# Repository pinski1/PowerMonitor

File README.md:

# Power Monitor
I wanted to monitor the current and voltage of some battery packs as I discharged them. As the battery packs were >36V fully charged there was no available board to do this easily. So here's one that's good for up to 80V.

This project is an entry into the [Hackaday.io](Hackaday.io) [Square Inch Project](https://hackaday.io/contest/160135-the-return-of-the-square-inch-project) Contest.

## Detailed Description

This project makes use of the Analog Devices [LTC4151](http://www.analog.com/en/products/monitor-control-protection/power-monitors/ltc4151.html) to measure the voltage, current and communicate these values over an I<sup>2</sup>C bus. In addition the LTC4151 will also calculate the instantaneous power and read an auxilary ADC input, in my board I've set this to be a temperature sensor.

### I<sup>2</sup>C Address
By default the I<sup>2</sup>C address is set to 0xD4 but if you wish to change it please consult this table:

|JP1|JP2|Address|
|----|----|----|
|X|X|0xCC|
|L|H|0xCE|
|H|NC|0xD0|
|H|H|0xD2|
|NC|NC|0xD4|
|L|NC|0xD6|
|H|L|0xD8|
|NC|H|0xDA|
|NC|L|0xDC|
|L|L|0xDE|

### Registers

|Register Address|Register Name|Read/Write|Description|
|--|--|--|--|
|0x00|SENSE (A)|R/W|ADC Current Sense Voltage Data (8 MSBs)|
|0x01|SENSE (B)|R/W|ADC Current Sense Voltage Data (4 LSBs)|
|0x02|VIN (C)|R/W|ADC VIN Voltage Data (8 MSBs)|
|0x03|VIN (D)|R/W|ADC VIN Voltage Data (4 LSBs)|
|0x04|ADIN (E)|R/W|ADC ADIN Voltage Data (8 MSBs)|
|0x05|ADIN (F)|R/W|ADC ADIN Voltage Data (4 LSBs)|
|0x06|CONTROL(G)|R/W|Controls ADC Operation Mode and Test Mode|
|0x07-0xFF|Reserved|N/A|Remaining addresses reserved|

Note: Registers A-F are only writeable if bit G4 is set.

### Calculating Current

+7V to +80V input range
81.92mV V_sense maximum
0R002 => 40.96A maximum
0R002 3.2W resistor 

### Calculating Temperature
[Thermistor](http://uk.farnell.com/panasonic-electronic-components/ertj1vs104fa/thermistor-ntc-0603-100k/dp/1892612)

## Licence
<br />This work is licensed under a <a rel="license" href="http://creativecommons.org/licenses/by-sa/4.0/">Creative Commons Attribution-ShareAlike 4.0 International License</a>.

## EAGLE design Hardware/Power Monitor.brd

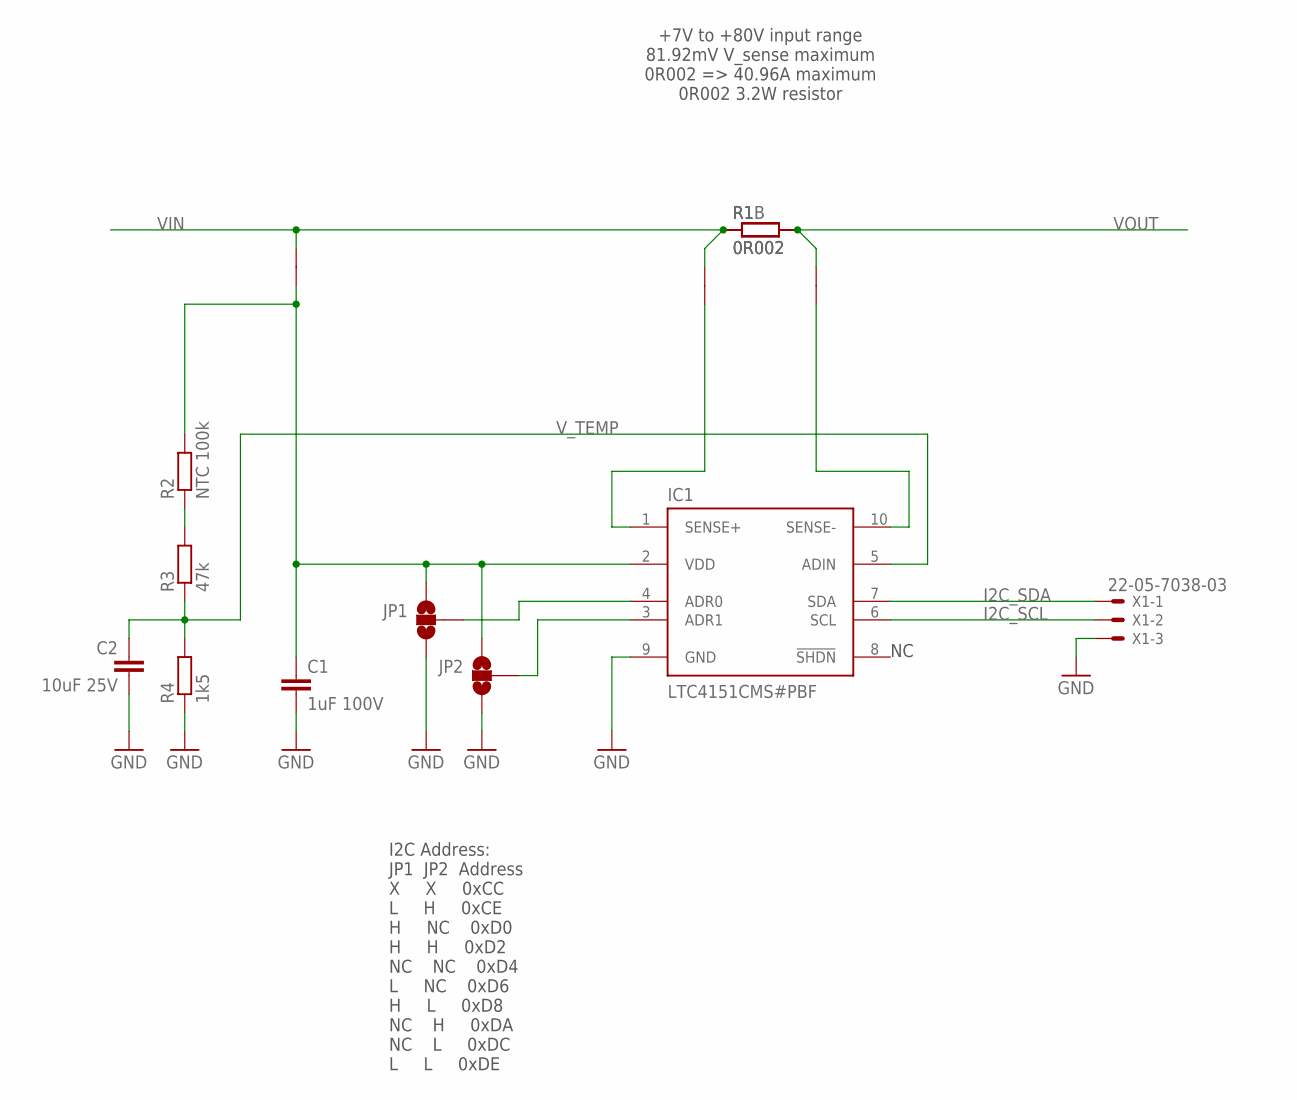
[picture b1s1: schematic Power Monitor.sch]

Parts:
C1: 1uF 100V; C0603
C2: 10uF 25V; C0603
IC1: LTC4151CMS#PBF; MSOP10
JP1, JP2: JUMPER-SMT_3_NO_SILK; SMT-JUMPER_3_NO_SILK
R1, R1B: 0R002; R2512; FARNELL_OC 2709404
R2: NTC 100k; R0603
R3: 47k; R0603
R4: 1k5; R0603
U$2, U$3, U$4: SHORT-002; 2X2
X1: 22-05-7038-03; 7395-03

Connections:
GND: C1.2, C2.2, IC1.9 (GND), JP1.3, JP2.3, R4.1, X1.3
I2C_SCL: IC1.6 (SCL), X1.2
I2C_SDA: IC1.7 (SDA), X1.1
unnamed: IC1.4 (ADR0), JP1.2
unnamed: IC1.3 (ADR1), JP2.2
unnamed: R2.1, R3.2
SEN_N: IC1.10 (SENSE-), U$3.1
SEN_P: IC1.1 (SENSE+), U$2.1
VDD: C1.1, IC1.2 (VDD), JP1.1, JP2.1, R2.2, U$4.1
VIN: R1.1, R1B.1, U$2.2, U$4.2
VOUT: R1.2, R1B.2, U$3.2
V_TEMP: C2.1, IC1.5 (ADIN), R3.1, R4.2

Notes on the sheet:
+7V to +80V input range 81.92mV V_sense maximum 0R002 => 40.96A maximum 0R002 3.2W resistor
I2C Address: JP1 JP2 Address X X 0xCC L H 0xCE H NC 0xD0 H H 0xD2 NC NC 0xD4 L NC 0xD6 H L 0xD8 NC H 0xDA NC L 0xDC L L 0xDE

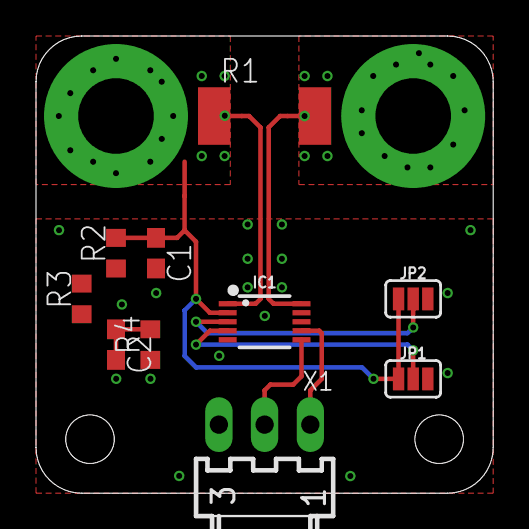
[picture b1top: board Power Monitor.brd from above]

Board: 2 copper layers, 25.4 x 25.4 mm, 14 parts (1 on the bottom side), 12 nets.

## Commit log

2018-08-10 Initial schematic & board checkin.

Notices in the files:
parts and their libraries:
SparkFun-IC-Power: Licensing: Creative Commons ShareAlike 4.0 International - https://creativecommons.org/licenses/by-sa/4.0
